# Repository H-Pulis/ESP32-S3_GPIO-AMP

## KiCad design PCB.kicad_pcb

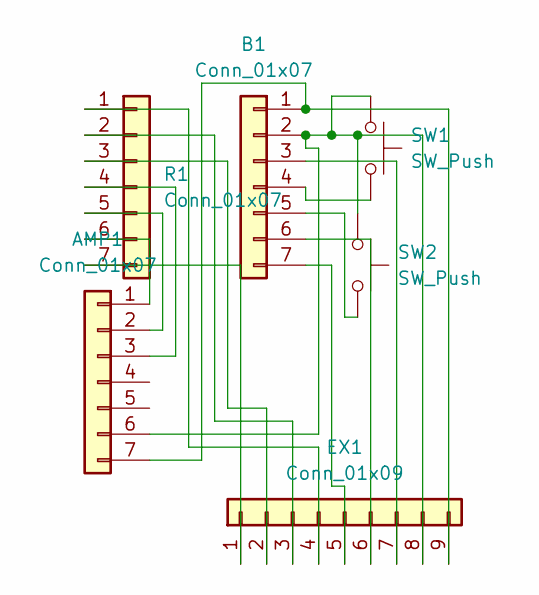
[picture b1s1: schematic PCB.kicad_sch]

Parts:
AMP1: Conn_01x07; PinHeader_1x07_P2.54mm_Vertical
B1: Conn_01x07; PinHeader_1x07_P2.54mm_Vertical
EX1: Conn_01x09; PinHeader_1x09_P2.54mm_Vertical
R1: Conn_01x07; PinHeader_1x07_P2.54mm_Vertical
SW1, SW2: SW_Push; SW_PUSH-12mm

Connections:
unnamed: AMP1.2 (BLCK), R1.5 (GPIO5)
unnamed: AMP1.3 (DIN), R1.4 (GPIO4)
unnamed: AMP1.6 (GND), B1.2 (GND), EX1.8, SW1.1, SW2.1
unnamed: AMP1.1 (LRC), R1.6 (GPIO6)
unnamed: AMP1.7 (VIN), B1.1 (5V), EX1.9
unnamed: B1.3 (3V3), EX1.7
unnamed: B1.6 (GPIO7), EX1.6
unnamed: B1.5 (GPIO8), SW2.2
unnamed: B1.4 (GPIO9), SW1.2
unnamed: B1.7 (GPIO44), EX1.5
unnamed: EX1.1, R1.7 (GPIO43)
unnamed: EX1.2, R1.3 (GPIO3)
unnamed: EX1.3, R1.2 (GPIO2)
unnamed: EX1.4, R1.1 (GPIO1)

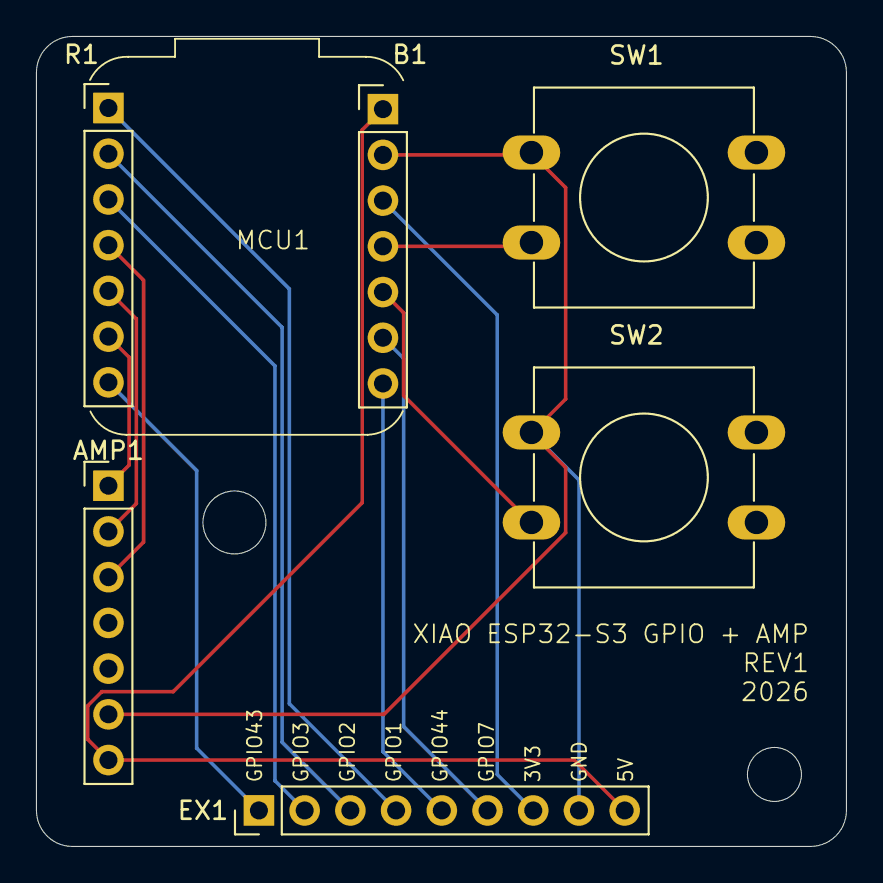
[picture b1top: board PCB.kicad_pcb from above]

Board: 2 copper layers, 45.0 x 45.0 mm, 7 parts (0 on the bottom side), 14 nets.

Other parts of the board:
H1: MountingHole; MountingHole_3.5mm

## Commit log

2026-03-03 add Kicad files
2026-03-03 Update PCB.kicad_pcb
    Added GitHub link
2026-03-03 Update file structure
